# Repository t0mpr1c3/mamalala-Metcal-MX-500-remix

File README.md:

# Sources

This is the work of Christian Klippel (mamalala on EEVblog) in 2012-2013, with input from other users on the forum. This repository is an attempt to collate information punlished in the main project thread, https://www.eevblog.com/forum/projects/diy-metcal-13-56-mhz-rf-supply/

I haven't attempted to build the project myself and have no specialist knowledge to bring to bear.

## richard.cs build

http://randomfunprojects.co.uk/metcal.html

### Comment in post #374

"Whilst you could use the original gerbers I would suggest a few changes:
1) Add in pads for the extra 56 pF capacitor.
2) Put some thermal relief in. I've found a lot of areas where something that carries no real current (DC or RF) like a logic pulldown is unsolderable with a small iron because one end is hard-down onto a large area of ground plane.
3) Consider swapping the LCD pinout to the standard one.
4) A little bit of BOM rationalisation would be nice. For example the Aux supply capacitor for the switcher (can't remember the number now) is currently the only 1206 10nF in the design and could have been the same as the 10nF 0805's scattered everywhere.
5) Depending on your skill with surface mount soldering the pads might benefit from tweaking slightly - they're perfect for reflow but a little tight for hand work."

### Comment in post #375

"The mounting holes on the board are 3.2 mm, this is a perfectly normal size for clearance M3 but I suspect that for many people with an electronics-only background getting four tapped holes in position to within perhaps 0.2 mm will be difficult, and being tapped the heatsink holes can't simply be opened out a little bigger. Might I suggest that loose-fitting 3.5 mm or even 4 mm holes might be preferable on a future board revision."

### Comment in post #512

"I built [my toroids] as per the schematic and notes, with 1uH, 1uH, 400n, 11 turns on a T80, 14 turns on a T50 and then 10 on the next T50. It works well and I've made no attempt to optimise it further."

## See also

- https://hackaday.com/2019/06/16/homemade-magic-makes-the-metcal-go/
- https://habr.com/en/post/451246/
- https://github.com/SergeyMax/SolderingStation
- https://www.eevblog.com/forum/reviews/metcal-mx-5200-and-mx-5000-firmware-and-data-eeprom-information/

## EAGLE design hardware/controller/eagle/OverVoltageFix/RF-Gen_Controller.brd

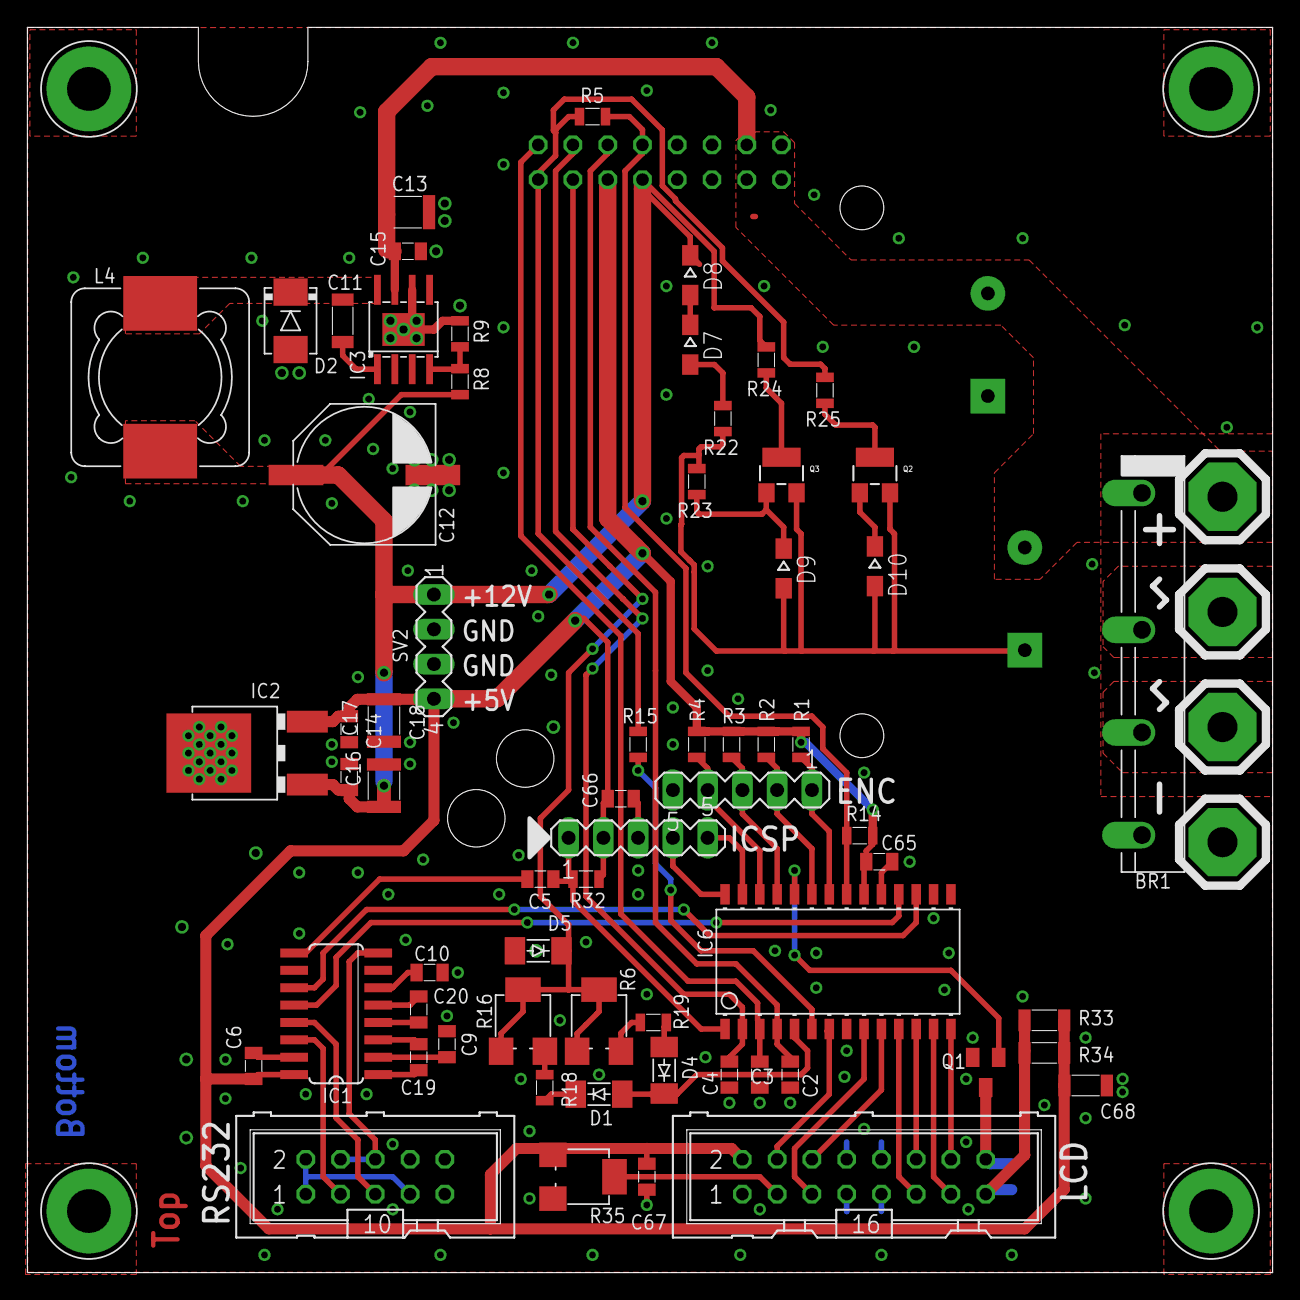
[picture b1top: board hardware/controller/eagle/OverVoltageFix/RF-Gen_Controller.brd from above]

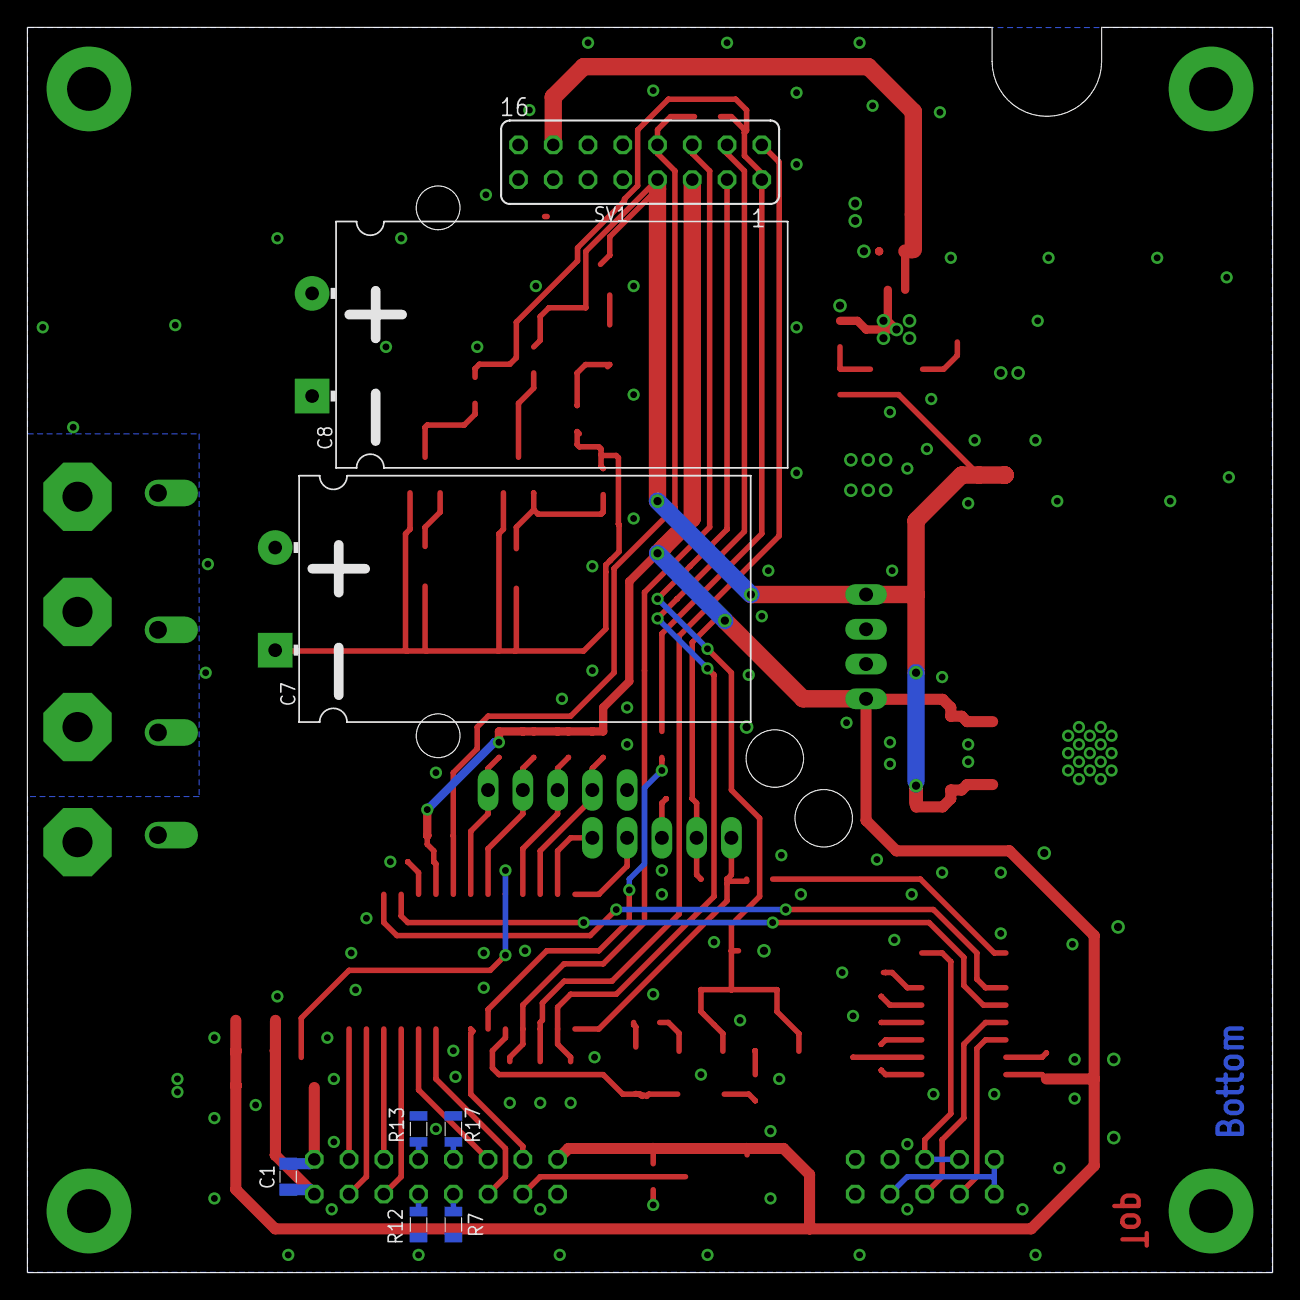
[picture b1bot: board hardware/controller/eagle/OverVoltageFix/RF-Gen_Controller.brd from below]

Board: 2 copper layers, 91.0 x 91.0 mm, 80 parts (8 on the bottom side), 60 nets.

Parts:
BR1: RECTIFIERGBJ_THT; GBJ_THT
C1, C2, C3, C4, C5, C6, C9, C10, C14, C15, C17, C19, C20, C65, C66, C67: 100n; C_0805_REFLOW
C7, C8: 2200µ/50V; CAP_EEUHD1H_VERT2
C11: 10n; C_1206_REFLOW
C12: 150µ/16V; CAP_AL_100_108
C13: 2µ2/50V; C_1210_REFLOW
C16: 4µ7/16V; C_1210_REFLOW
C18: 2µ2/16V; C_1210_REFLOW
C68: 22µ; C_1206_REFLOW
D1, D4: 1N4148; LL-34
D2: SMB
D5: Z5.6; LL-34
D7: 10V; SOD323-W
D8: 12V; SOD323-W
D9, D10: 5V6; SOD323-W
ENC: MA05-1
IC1: SN65C3232SO16; SO16
IC2: DPAK-3
IC3: TPS5430SO-8-PP; SO-8-PP
IC6: PIC18F2620SOIC-28; SOIC-28
ICSP: MA05-1
L4: 47µ; SSR1260
LCD: ML16
PAD1, PAD2, PAD7, PAD8: SOLPAD_5
Q1: 2N7002; SOT23
Q2, Q3: 2N7000; SOT23-W
R1, R2, R3, R4, R7, R12, R13, R17, R24: 22k; R_0805_REFLOW
R5: 0; R_0805_REFLOW
R6, R16, R35: 10k; 3364W
R8: 10k; R_0805_REFLOW
R9: 1k13; R_0805_REFLOW
R14, R32: 47k; R_0805_REFLOW
R15, R23, R25: 1k; R_0805_REFLOW
R18, R19: ***; R_0805_REFLOW
R22: 2k2; R_0805_REFLOW
R33, R34: 10; R_1206_REFLOW
RS232: ML10
SV1: FE08-2
SV2: MA04-1
U$6, U$7, U$8, U$9: MOUNTPADM3_WASHER; PAD_M3_WASHER

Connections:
232_RX: IC1.12, IC6.18
232_TX: IC1.11, IC6.17
+12V: C12.+, C16.P$1, C17.P$1, D8.C, IC2.1, L4.1, R8.P$2, R24.P$2, SV1.7, SV2.1
/MCLR: C5.P$1, IC6.1, ICSP.1, R32.P$1
AC1: BR1.AC1, PAD7.P$1
AC2: BR1.AC2, PAD8.P$1
BL_A: C1.P$2, LCD.15, R33.P$2, R34.P$2
BL_PWM: IC6.24, Q1.1
DB4: IC6.11, LCD.11
DB5: IC6.12, LCD.12
DB6: IC6.13, LCD.13
DB7: IC6.14, LCD.14
DETECT: RS232.1, RS232.2, RS232.7
E: IC6.10, LCD.6
GND: BR1.-, C2.P$2, C3.P$2, C4.P$2, C6.P$2, C7.-, C8.-, C9.P$1, C10.P$1, C12.-, C13.P$2, C14.P$2, C15.P$2, C16.P$2, C17.P$2, C18.P$2, C65.P$2, C66.P$2, C67.P$2, C68.P$2, D2.A, D5.A, D9.A, D9.C, D10.A, ENC.5, IC1.15, IC2.4, IC3.6, IC3.EP, IC6.8, IC6.19, ICSP.3, LCD.1, PAD2.P$1, Q1.2, Q2.2, Q3.1, Q3.2, R7.P$2, R9.P$1, R12.P$2, R13.P$2, R17.P$2, R22.P$1, R23.P$1, R23.P$2, R35.E, RS232.9, SV1.9, SV1.10, SV1.11, SV1.12, SV2.2, SV2.3, U$6.P$1, U$7.P$1, U$8.P$1, U$9.P$1
LED_K: C1.P$1, LCD.16, Q1.3
unnamed: R6.E, R19.P$1
unnamed: R16.E, R18.P$1
unnamed: LCD.9, R12.P$1
unnamed: LCD.7, R7.P$1
unnamed: LCD.10, R13.P$1
unnamed: C9.P$2, IC1.2
unnamed: C5.P$2, IC1.9
unnamed: C10.P$2, IC1.6
unnamed: C11.P$1, IC3.1
unnamed: IC3.4, R8.P$1, R9.P$2
unnamed: C19.P$1, IC1.3
unnamed: C20.P$1, IC1.5
unnamed: LCD.8, R17.P$1
unnamed: D1.C, R18.P$2
unnamed: D4.A, R19.P$2
unnamed: C20.P$2, IC1.4
unnamed: C19.P$2, IC1.1
PGC: IC6.27, ICSP.5
PGD: IC6.28, ICSP.4
REG: C2.P$1, IC6.4, SV1.6
RF_EN: IC6.6, R15.P$2
RF_EN_OUT: C6.P$1, C14.P$1, C18.P$1, C65.P$1, C66.P$1, C67.P$1, C68.P$1, IC1.16, IC2.3, IC6.20, ICSP.2, LCD.2, R1.P$2, R2.P$2, R3.P$2, R4.P$2, R5.P$2, R14.P$2, R15.P$1, R25.P$2, R32.P$2, R33.P$1, R34.P$1, R35.A, SV1.1, SV1.5, SV2.4
RS: IC6.7, LCD.4
RW: IC6.9, LCD.5
RX: IC1.13, RS232.5
S$2: D7.A, R22.P$2
S$3: D7.C, D8.A
S$7: D10.C, Q2.1
S$8: Q3.3, R24.P$1
S$9: Q2.3, R25.P$1
SRESET: IC1.8, RS232.4, RS232.6
SW12: C11.P$2, D2.C, IC3.8, L4.2
TA: ENC.1, IC6.22, R1.P$1
TB: ENC.2, IC6.23, R2.P$1
TC: ENC.3, IC6.25, R3.P$1
TD: ENC.4, IC6.26, R4.P$1
TIP_DET: IC6.21, R5.P$1, R14.P$1, SV1.8
TX: IC1.14, RS232.3
VF: C4.P$1, IC6.2, SV1.4
VIN: BR1.+, C7.+, C8.+, C13.P$1, C15.P$1, IC3.7, PAD1.P$1, SV1.13, SV1.14, SV1.15, SV1.16
VLIM: D5.C, R6.A, R6.S, R16.A, R16.S, SV1.3
VLIM_OUT: D1.A, D4.C, IC6.5
VO: LCD.3, R35.S
VR: C3.P$1, IC6.3, SV1.2

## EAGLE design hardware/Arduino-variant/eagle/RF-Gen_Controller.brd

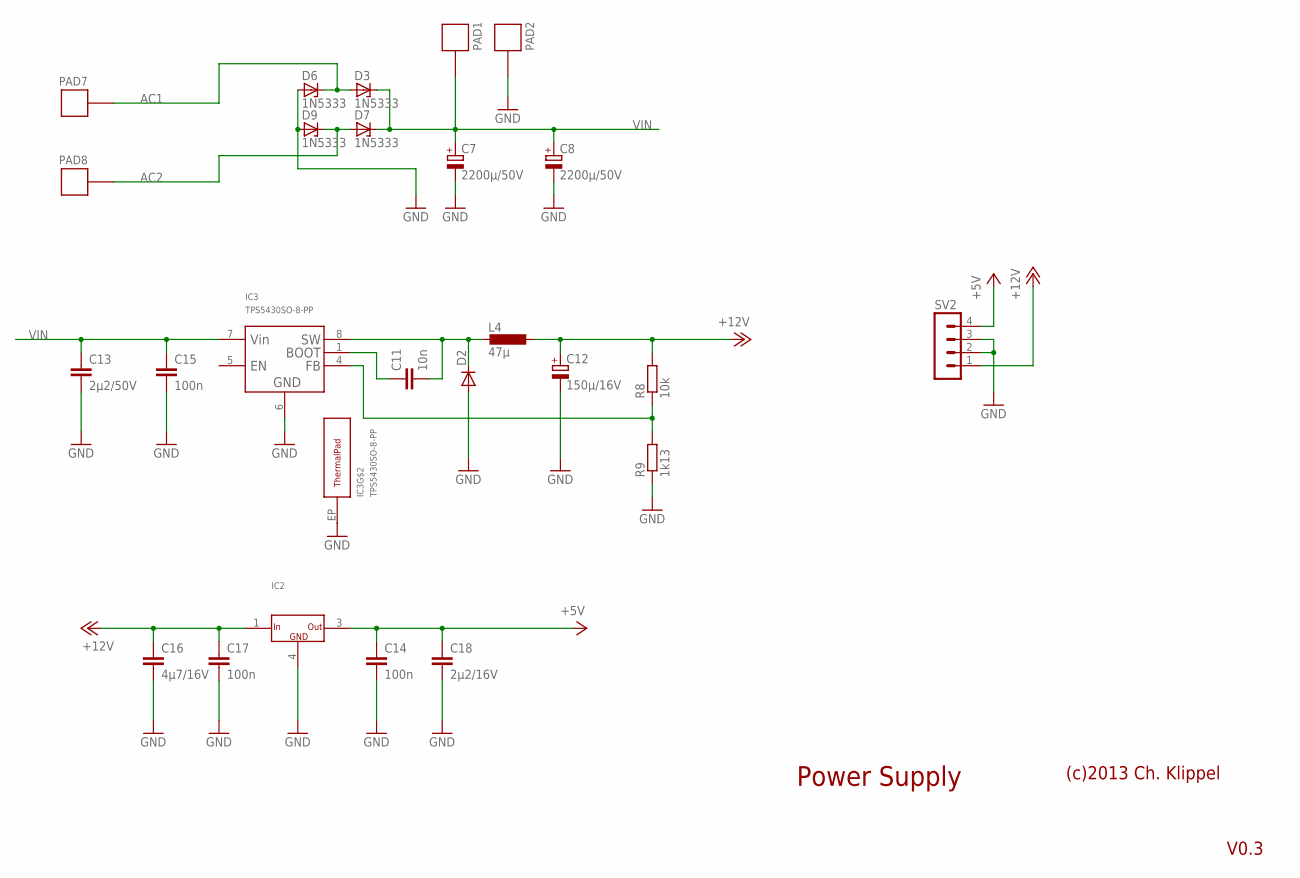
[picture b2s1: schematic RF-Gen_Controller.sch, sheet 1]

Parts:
C7, C8: 2200µ/50V; CAP_EEUHD1H_VERT2
C11: 10n; C_1206_REFLOW
C12: 150µ/16V; CAP_AL_100_108
C13: 2µ2/50V; C_1210_REFLOW
C14, C15, C17: 100n; C_0805_REFLOW
C16: 4µ7/16V; C_1210_REFLOW
C18: 2µ2/16V; C_1210_REFLOW
D2: DIODE-SMB; SMB
D3, D6, D7, D9: 1N5333; C1702-15
IC2: VREG_3DPAK-3; DPAK-3
IC3: TPS5430SO-8-PP; SO-8-PP
L4: 47µ; SSR1260
PAD1, PAD2, PAD7, PAD8: SOLPAD5MM; SOLPAD_5
R8: 10k; R_0805_REFLOW
R9: 1k13; R_0805_REFLOW
SV2: MA04-1

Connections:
+5V: C14.P$1 (1), C18.P$1 (1), IC2.3 (OUT), SV2.4; also elsewhere on the board
+12V: C12.+, C16.P$1 (1), C17.P$1 (1), IC2.1 (IN), L4.1, R8.P$2 (2), SV2.1; also elsewhere on the board
AC1: D3.A, D6.C, PAD7.P$1
AC2: D7.A, D9.C, PAD8.P$1
GND: C7.-, C8.-, C12.-, C13.P$2 (2), C14.P$2 (2), C15.P$2 (2), C16.P$2 (2), C17.P$2 (2), C18.P$2 (2), D2.A, D6.A, D9.A, IC2.4 (GND), IC3.6 (GND), IC3.EP (THERMALPAD), PAD2.P$1, R9.P$1 (1), SV2.2, SV2.3; also elsewhere on the board
unnamed: C11.P$1 (1), IC3.1 (BOOT)
unnamed: IC3.4 (FB), R8.P$1 (1), R9.P$2 (2)
SW12: C11.P$2 (2), D2.C, IC3.8 (SW), L4.2
VIN: C7.+, C8.+, C13.P$1 (1), C15.P$1 (1), D3.C, D7.C, IC3.7 (VIN), PAD1.P$1; also elsewhere on the board

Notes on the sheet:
Power Supply
(c)2013 Ch. Klippel
V0.3

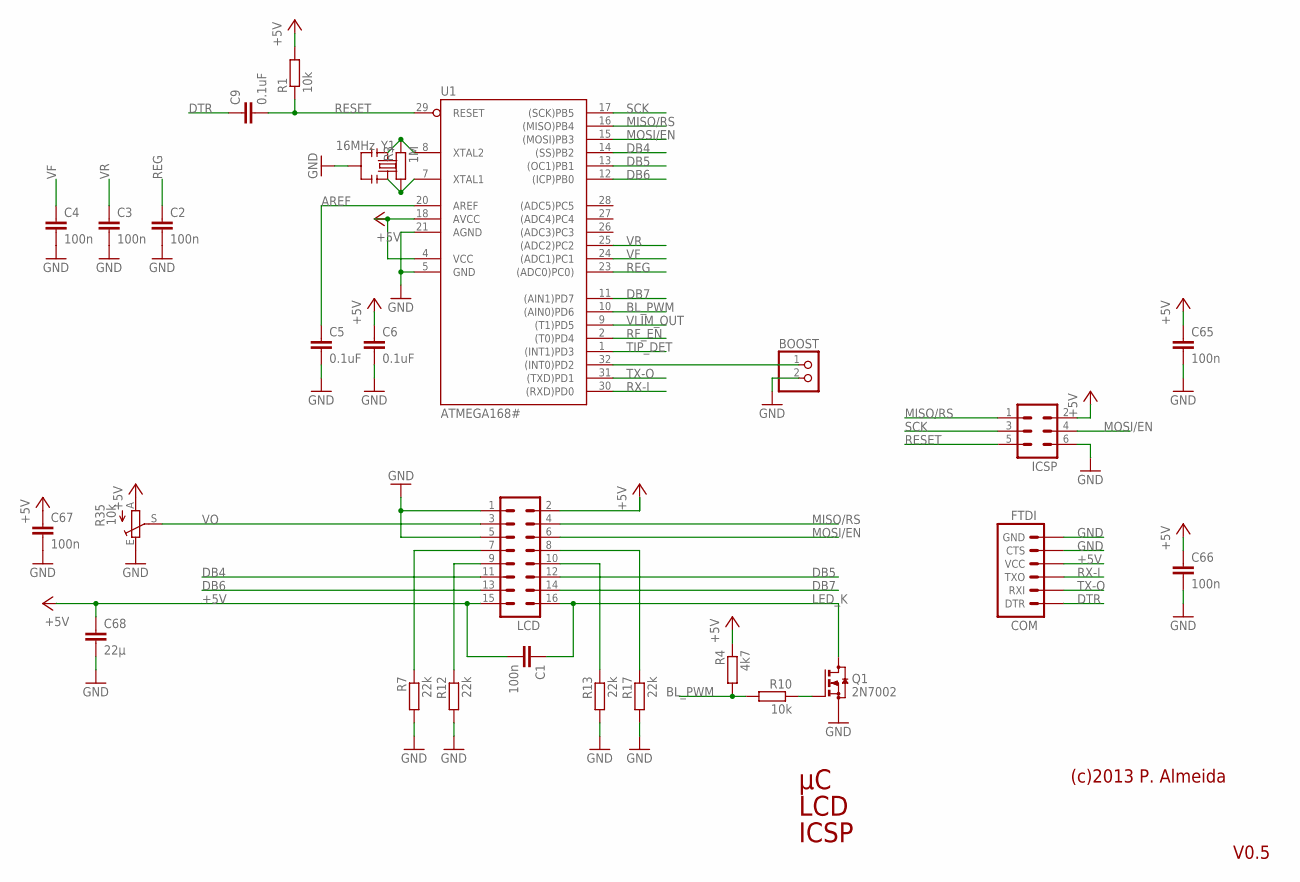
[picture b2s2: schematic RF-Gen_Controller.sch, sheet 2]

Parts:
BOOST: PINHD-1X2/90; 1X02/90
C1, C2, C3, C4, C65, C66, C67: 100n; C_0805_REFLOW
C5, C6, C9: 0.1uF; C_0805_REFLOW
C68: 22µ; C_1206_REFLOW
FTDI: COM; 1X06
ICSP: ML6
LCD: ML16
Q1: 2N7002; SOT23
R1, R10: 10k; R_0805_REFLOW
R3: 1M; R_0805_REFLOW
R4: 4k7; R_0805_REFLOW
R7, R12, R13, R17: 22k; R_0805_REFLOW
R35: 10k; 3364W
U1: ATMEGA168#; TQFP32-08
Y1: 16MHz; RESONATOR-SMD

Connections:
+5V: C1.P$2 (2), C6.P$1 (1), C65.P$1 (1), C66.P$1 (1), C67.P$1 (1), C68.P$1 (1), FTDI.4 (VCC), ICSP.2, LCD.2, LCD.15, R1.P$2 (2), R4.P$1 (1), R35.A, U1.4 (VCC), U1.18 (AVCC); also elsewhere on the board
AREF: C5.P$1 (1), U1.20 (AREF)
BL_PWM: R4.P$2 (2), R10.P$2 (2), U1.10 ((AIN0)PD6)
DB4: LCD.11, U1.14 ((SS)PB2)
DB5: LCD.12, U1.13 ((OC1)PB1)
DB6: LCD.13, U1.12 ((ICP)PB0)
DB7: LCD.14, U1.11 ((AIN1)PD7)
DTR: C9.P$1 (1), FTDI.1 (DTR)
GND: BOOST.2, C2.P$2 (2), C3.P$2 (2), C4.P$2 (2), C5.P$2 (2), C6.P$2 (2), C65.P$2 (2), C66.P$2 (2), C67.P$2 (2), C68.P$2 (2), FTDI.5 (CTS), FTDI.6 (GND), ICSP.6, LCD.1, LCD.5, Q1.2 (S), R7.P$2 (2), R12.P$2 (2), R13.P$2 (2), R17.P$2 (2), R35.E, U1.5 (GND), U1.21 (AGND), Y1.2; also elsewhere on the board
LED_K: C1.P$1 (1), LCD.16, Q1.3 (D)
MISO/RS: ICSP.1, LCD.4, U1.16 ((MISO)PB4)
MOSI/EN: ICSP.4, LCD.6, U1.15 ((MOSI)PB3)
unnamed: LCD.9, R12.P$1 (1)
unnamed: LCD.7, R7.P$1 (1)
unnamed: LCD.10, R13.P$1 (1)
unnamed: Q1.1 (G), R10.P$1 (1)
unnamed: BOOST.1, U1.32 ((INT0)PD2)
unnamed: R3.P$1 (1), U1.8 (XTAL2), Y1.1
unnamed: R3.P$2 (2), U1.7 (XTAL1), Y1.3
unnamed: LCD.8, R17.P$1 (1)
REG: C2.P$1 (1), U1.23 ((ADC0)PC0)); also elsewhere on the board
RESET: C9.P$2 (2), ICSP.5, R1.P$1 (1), U1.29 (RESET)
RF_EN: U1.2 ((T0)PD4); also elsewhere on the board
RX-I: FTDI.3 (TXO), U1.30 ((RXD)PD0)
SCK: ICSP.3, U1.17 ((SCK)PB5)
TIP_DET: U1.1 ((INT1)PD3); also elsewhere on the board
TX-O: FTDI.2 (RXI), U1.31 ((TXD)PD1)
VF: C4.P$1 (1), U1.24 ((ADC1)PC1); also elsewhere on the board
VLIM_OUT: U1.9 ((T1)PD5); also elsewhere on the board
VO: LCD.3, R35.S
VR: C3.P$1 (1), U1.25 ((ADC2)PC2); also elsewhere on the board

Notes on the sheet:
LCD
ICSP
(c)2013 P. Almeida
V0.5

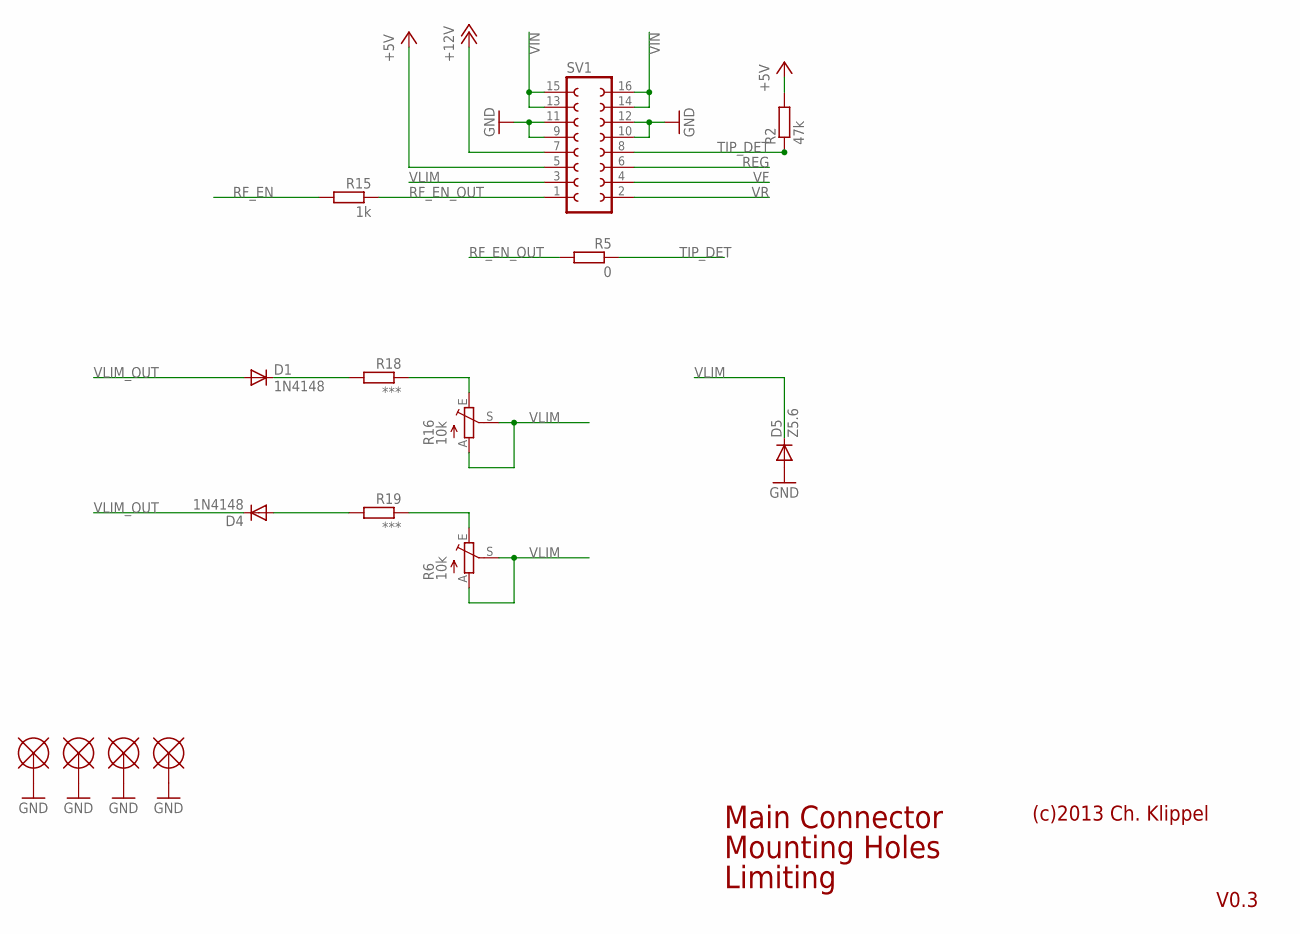
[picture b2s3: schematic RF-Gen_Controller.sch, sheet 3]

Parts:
D1, D4: 1N4148; LL-34
D5: Z5.6; LL-34
R2: 47k; R_0805_REFLOW
R5: 0; R_0805_REFLOW
R6, R16: 10k; 3364W
R15: 1k; R_0805_REFLOW
R18, R19: ***; R_0805_REFLOW
SV1: FE08-2
U$6, U$7, U$8, U$9: MOUNTPADM3_WASHER; PAD_M3_WASHER

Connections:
+5V: R2.P$2 (2), SV1.5; also elsewhere on the board
+12V: SV1.7; also elsewhere on the board
GND: D5.A, SV1.9, SV1.10, SV1.11, SV1.12, U$6.P$1, U$7.P$1, U$8.P$1, U$9.P$1; also elsewhere on the board
unnamed: R6.E, R19.P$1 (1)
unnamed: R16.E, R18.P$1 (1)
unnamed: D1.C, R18.P$2 (2)
unnamed: D4.A, R19.P$2 (2)
REG: SV1.6; also elsewhere on the board
RF_EN: R15.P$2 (2); also elsewhere on the board
RF_EN_OUT: R5.P$2 (2), R15.P$1 (1), SV1.1
TIP_DET: R2.P$1 (1), R5.P$1 (1), SV1.8; also elsewhere on the board
VF: SV1.4; also elsewhere on the board
VIN: SV1.13, SV1.14, SV1.15, SV1.16; also elsewhere on the board
VLIM: D5.C, R6.A, R6.S, R16.A, R16.S, SV1.3
VLIM_OUT: D1.A, D4.C; also elsewhere on the board
VR: SV1.2; also elsewhere on the board

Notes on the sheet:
Main Connector
Mounting Holes
Limiting
(c)2013 Ch. Klippel
V0.3

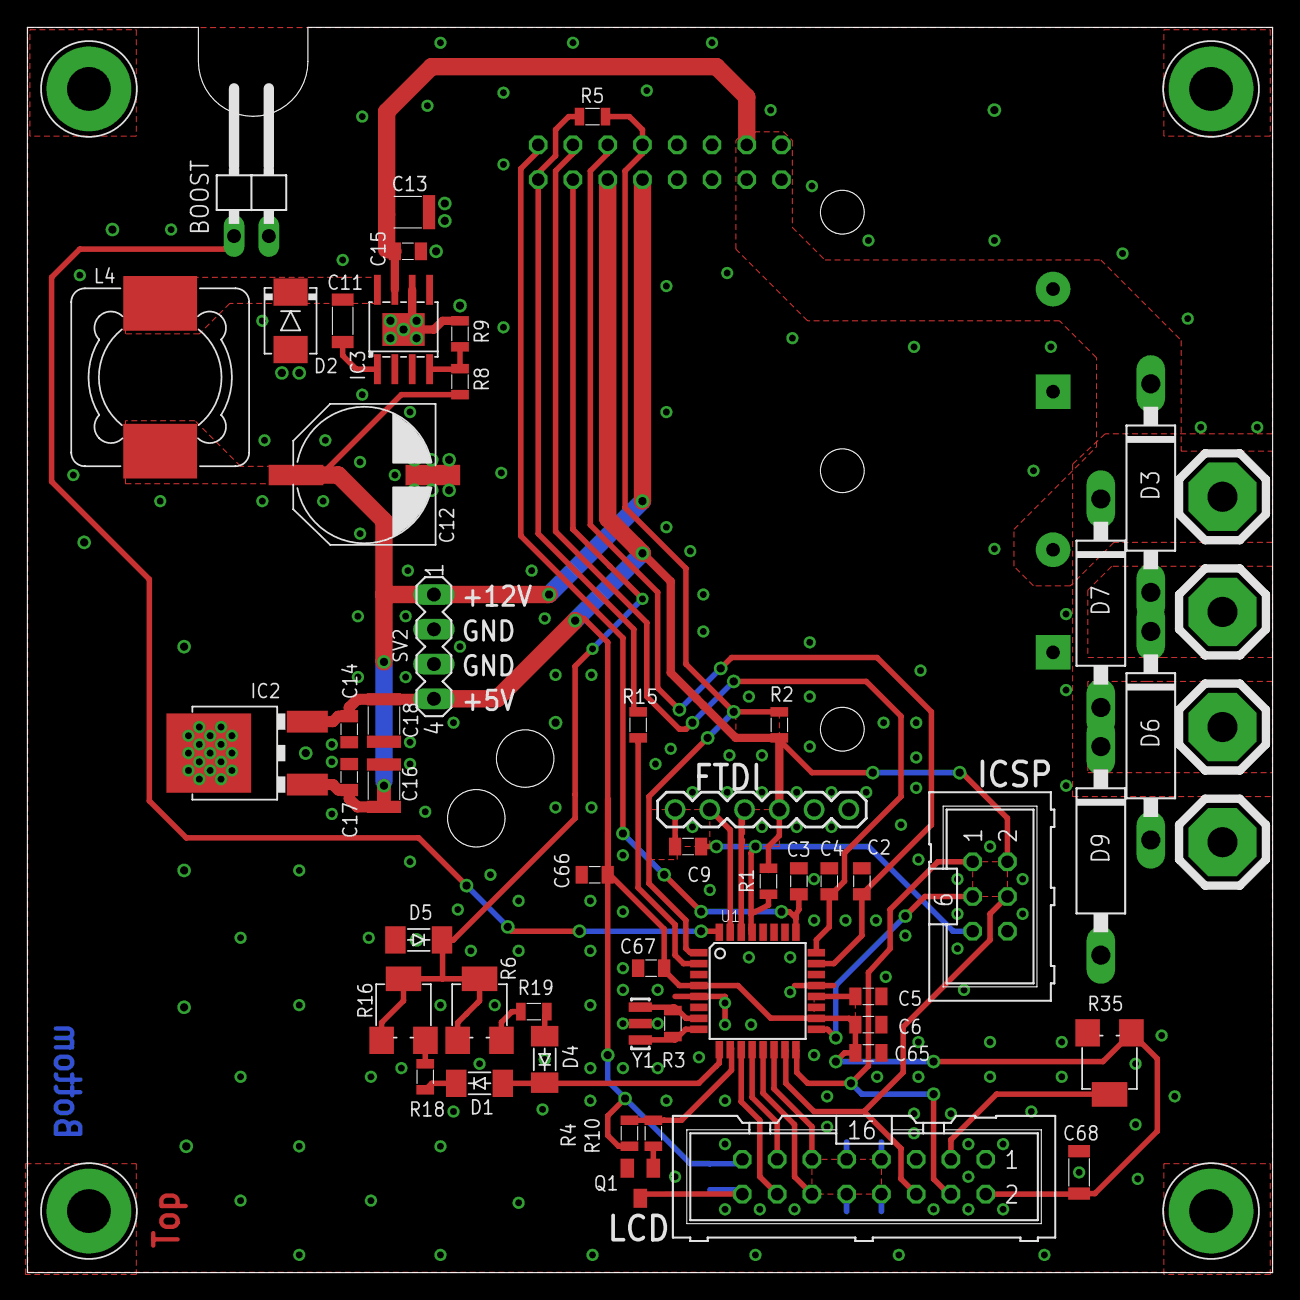
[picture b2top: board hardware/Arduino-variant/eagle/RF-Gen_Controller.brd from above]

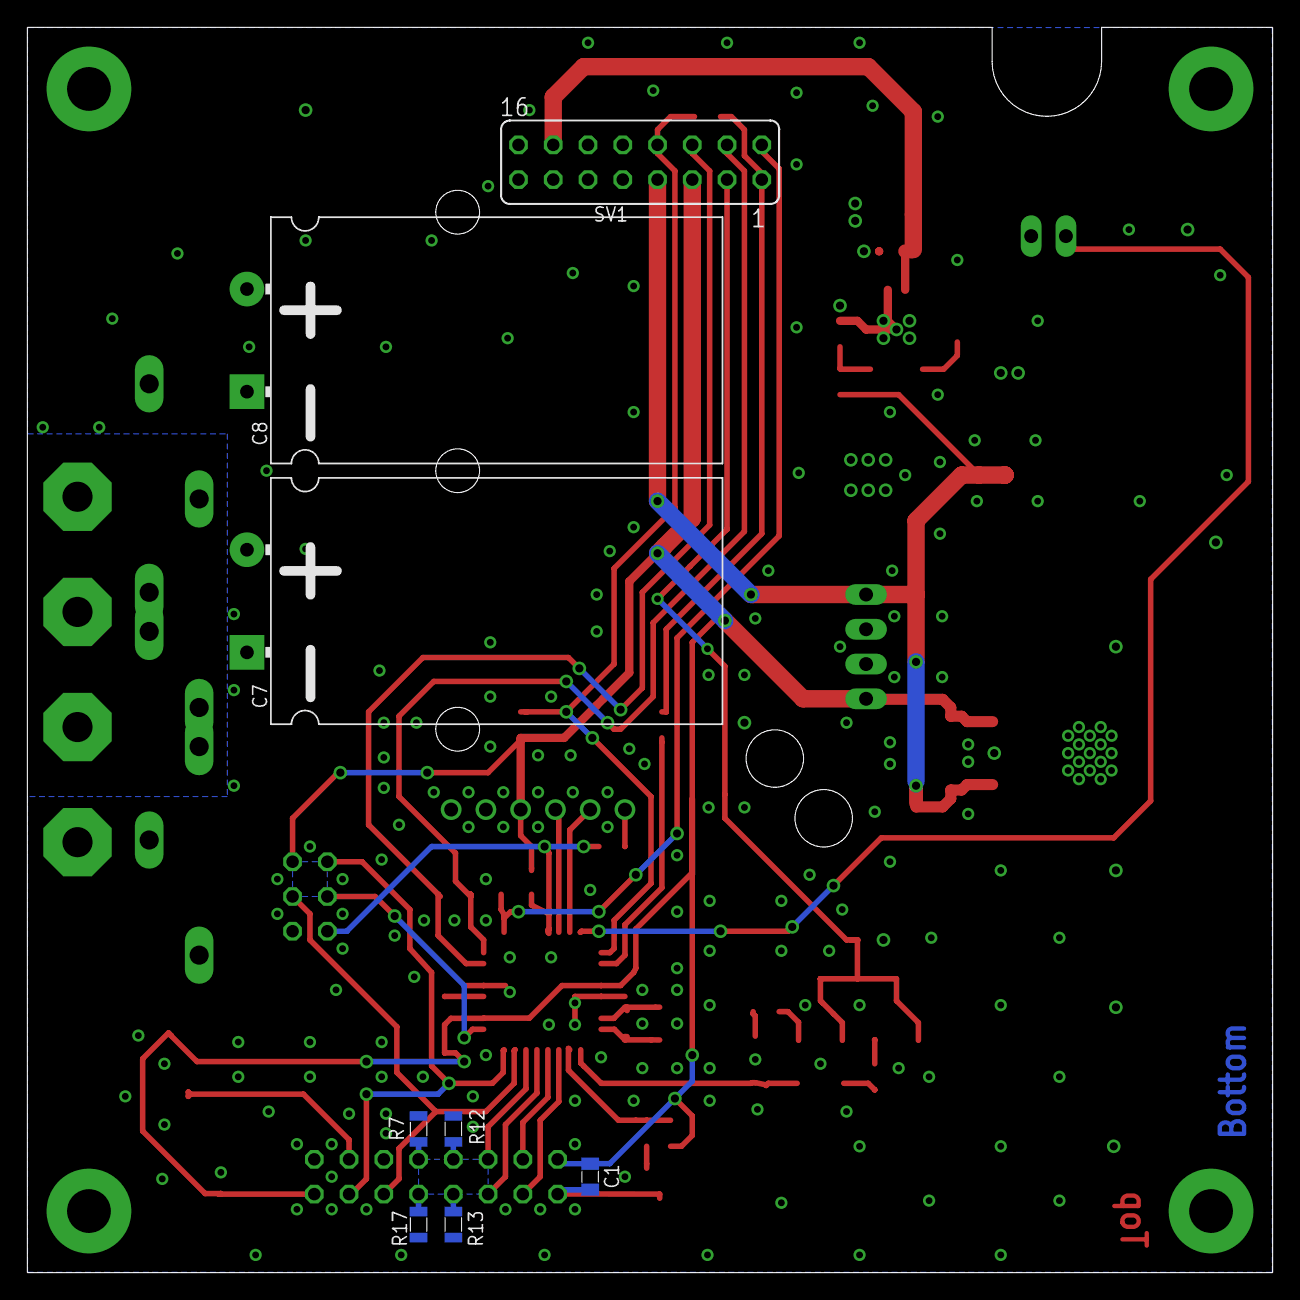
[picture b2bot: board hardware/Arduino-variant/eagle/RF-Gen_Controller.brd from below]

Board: 2 copper layers, 91.0 x 91.0 mm, 67 parts (8 on the bottom side), 44 nets.

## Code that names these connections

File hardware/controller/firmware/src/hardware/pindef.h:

/*
 * (c) 2013 Ch. klippel  -  ck@atelier-klippel.de / c.klippel@gmx.de
 *
 * This code is released under the terms of the GPL, version 2 or newer.
 * See the file COPYING for more information about the license.
 *
 * Changelog:
 *
 * v00.01: - Initial version
 *
 */

#ifndef PINDEF_H
#define PINDEF_H

#define PIN_IN		1
#define PIN_OUT		0

// 1 = in, 0 = out

#define CFG_TRISA	0b00001111;
#define CFG_LATA	0b00000000;

#define CFG_TRISB	0b00110111;
#define CFG_LATB	0b00000000;

#define CFG_TRISC	0b10000000;
#define CFG_LATC	0b00000000;

#define V_FORWARD_IN            PORTAbits.RA0
#define V_REFLECTED_IN          PORTAbits.RA1
#define V_REG_IN		PORTAbits.RA2

#define VLIM_OUT		LATAbits.LATA3
#define VLIM_DIR		TRISAbits.TRISA3

#define RFG_EN			LATAbits.LATA4

#define TIP_DET 		PORTBbits.RB0

#define ENC1_A			PORTBbits.RB1
#define ENC1_B			PORTBbits.RB2
#define ENC1_K			PORTBbits.RB4
#define ENC1_S			PORTBbits.RB5


#define BL			LATBbits.LATB3
#define BL_ON			1
#define BL_OFF			0

#define PGD				PORTBbits.RB7
#define PGC				PORTBbits.RB6

#define MCLR			PORTEbits.RE3

#endif

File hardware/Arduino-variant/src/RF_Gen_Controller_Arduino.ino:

#include <LiquidCrystal.h>

LiquidCrystal lcd(12, 11, 10, 9, 8, 7); // LiquidCrystal(rs, enable, d4, d5, d6, d7)

int TIP_DET_PIN           = 3;          // Digital PIN 0-13
int RF_EN_PIN             = 4;          // Digital PIN 0-13
int VLIM_PIN              = 5;          // Digital PIN 0-13
int BOOST_PIN             = 2;          // Digital PIN 0-13
int REG_PIN               = A0;         // Analog PIN A0-A5
int VF_PIN                = A1;         // Analog PIN A0-A5
int VR_PIN                = A2;         // Analog PIN A0-A5
int BACKLIGHT_PIN         = 6;          // PWM PIN 3, 5, 6, 9, 10, or 11

float VF, VR, REG, VSWR;

int SAMPLES               = 16;
int NO_TIP_BACKLIGHT_VAL  = 50;         // 0-255
int POWER_BACKLIGHT_VAL   = 255;        // 0-255
int BOOST_BACKLIGHT_VAL   = 255;        // 0-255
int READY_BACKLIGHT_VAL   = 255;        // 0-255
int ECO_BACKLIGHT_VAL     = 50;         // 0-255
int STANDBY_BACKLIGHT_VAL = 0;          // 0-255

int VSWR_MAX              = 1000;
int READY_VAL             = 10;         // 0-99
    
long ECO_TIME             = 5000;       // ms
long STANDBY_TIME         = 10000;      // ms
  
unsigned long LASTMILLIS;
int PERCENT, LASTPERCENT, STATE, LASTSTATE;

byte r0[8] = {
  B00000, 
  B00000,
  B00000,
  B00000,
  B00000,
  B00000,
  B00000,
  B00000
}; // 0 / 5
byte r1[8] = {
  B10000, 
  B10000,
  B10000,
  B10000,
  B10000,
  B10000,
  B10000,
  B10000
}; // 1 / 5
byte r2[8] = {
  B11000, 
  B11000,
  B11000,
  B11000,
  B11000,
  B11000,
  B11000,
  B11000
}; // 2 / 5 
byte r3[8] = {
  B11100, 
  B11100,
  B11100,
  B11100,
  B11100,
  B11100,
  B11100,
  B11100
}; // 3 / 5
byte r4[8] = {
  B11110, 
  B11110,
  B11110,
  B11110,
  B11110,
  B11110,
  B11110,
  B11110
}; // 4 / 5
byte r5[8] = {
  B11111, 
  B11111,
  B11111,
  B11111,
  B11111,
  B11111,
  B11111,
  B11111
}; // 5 / 5

void draw_state(int State) {
  
  if (State == 0){
      lcd.setCursor(4, 0);
      lcd.print("STANDBY");
      digitalWrite(RF_EN_PIN, LOW);
      analogWrite(BACKLIGHT_PIN, STANDBY_BACKLIGHT_VAL);}
      
  if (State == 1){
      lcd.setCursor(4, 0);
      lcd.print("  ECO  ");
      pinMode(VLIM_PIN, OUTPUT);
      digitalWrite(VLIM_PIN, HIGH);
      analogWrite(BACKLIGHT_PIN, ECO_BACKLIGHT_VAL);}
      
  if (State == 2){
      lcd.setCursor(4, 0);
      lcd.print(" READY ");
      pinMode(VLIM_PIN, INPUT);
      analogWrite(BACKLIGHT_PIN, READY_BACKLIGHT_VAL);}
      
  if (State == 3){
      lcd.setCursor(4, 0);
      lcd.print(" POWER ");
      pinMode(VLIM_PIN, INPUT);
      analogWrite(BACKLIGHT_PIN, POWER_BACKLIGHT_VAL);}
      
  if (State == 4){
      lcd.setCursor(4, 0);
      lcd.print(" BOOST ");
      digitalWrite(RF_EN_PIN, HIGH);
      pinMode(VLIM_PIN, OUTPUT);
      digitalWrite(VLIM_PIN, LOW);
      analogWrite(BACKLIGHT_PIN, BOOST_BACKLIGHT_VAL);}
      
  if (State == 5){
      lcd.setCursor(4, 0);
      lcd.print("NO  TIP");
      digitalWrite(RF_EN_PIN, LOW);
      analogWrite(BACKLIGHT_PIN, NO_TIP_BACKLIGHT_VAL);}
  
}

void draw_bargraph(int percent) {
  int i, cp, cl;

  if (percent < READY_VAL){
      lcd.setCursor(14, 1);
      lcd.print("0");
      lcd.print(percent);}
  else { 
      lcd.setCursor(14, 1);
      lcd.print(percent);}

  lcd.setCursor(0, 1);
  
  percent = map(percent, 0, 99, 0, 70);
  cp = percent / 5;
  cl = percent % 5;
  
  for(i = 0; i < cp; ++i)
    lcd.write(5);
  if(cl != 0)
    lcd.write(cl);

  for(i = 0; i < 14 - (cp + (cl ? 1 : 0)); ++i)
    lcd.write((uint8_t)0);
}

void setup(){
  
  Serial.begin(9600);
  pinMode(TIP_DET_PIN, INPUT);
  digitalWrite(TIP_DET_PIN, HIGH);
  pinMode(BOOST_PIN, INPUT);
  digitalWrite(BOOST_PIN, HIGH);
  pinMode(RF_EN_PIN, OUTPUT);
  pinMode(BACKLIGHT_PIN, OUTPUT);
  analogWrite(BACKLIGHT_PIN, BOOST_BACKLIGHT_VAL);
   
  lcd.createChar(0, r0);
  lcd.createChar(1, r1);
  lcd.createChar(2, r2);
  lcd.createChar(3, r3);
  lcd.createChar(4, r4);
  lcd.createChar(5, r5);

  lcd.begin(16, 2); 
  lcd.clear();
  lcd.setCursor(0, 0);
  lcd.print(" RF-GEN MX-5000 ");
  lcd.setCursor(0, 1);
  lcd.print("   Ver:  2.01   ");
  delay(3000);
  lcd.clear();
  
  PERCENT = 0;
  STATE = 4;
  draw_state(STATE);
  LASTSTATE = STATE;
  draw_bargraph(PERCENT);
  LASTPERCENT = PERCENT;
}

void loop(){
  
REG = 0;
VF  = 0;
VR  = 0;

for (int i = 0; i < SAMPLES; i++){
     REG = REG + analogRead(REG_PIN);
     VF  = VF + analogRead(VF_PIN);
     VR  = VR + analogRead(VR_PIN);
     delay(1);}
     
REG = REG / SAMPLES;
VF  = VF / SAMPLES;
VR  = VR / SAMPLES;

VSWR = (1 + sqrt(VR / VF)) / (1 - sqrt(VR / VF));
PERCENT = map(constrain(VSWR, 0, VSWR_MAX), 0, VSWR_MAX, 99, 0);

Serial.print("REG = ");
Serial.print(REG);
Serial.print("\tVF = ");
Serial.print(VF);
Serial.print("\tVR = ");
Serial.print(VR);
Serial.print("\tVSWR = ");
Serial.print(VSWR);
Serial.print("\tPERCENT = ");
Serial.println(PERCENT);

if (digitalRead(TIP_DET_PIN) == LOW) STATE = 5;                                                     //NO TIP 

else{  
  
if (digitalRead(BOOST_PIN) == LOW) STATE = 4;
  
else {
  
if (LASTPERCENT > PERCENT && LASTSTATE == 4 || PERCENT > READY_VAL && LASTSTATE != 4)  STATE = 3;   //POWER
if (PERCENT > READY_VAL && LASTSTATE == 1 || LASTSTATE == 5)                           STATE = 4;   //BOOST
if (PERCENT < READY_VAL && LASTSTATE != 1 && LASTSTATE != 4 && LASTSTATE != 5)         STATE = 2;   //READY
if (millis() - LASTMILLIS > ECO_TIME)                                                  STATE = 1;   //ECO
if (millis() - LASTMILLIS > STANDBY_TIME)                                              STATE = 0;   //STANDBY
}
}

if (PERCENT > READY_VAL || STATE == 4 || STATE == 5) LASTMILLIS = millis();

if (STATE != LASTSTATE){
    draw_state(STATE);
    LASTSTATE = STATE;}
  
if (PERCENT != LASTPERCENT){
    draw_bargraph(PERCENT);
    LASTPERCENT = PERCENT;}
  
delay(100);
}

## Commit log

2021-02-20 remove inconsistencies in build notes and BOM

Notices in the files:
hardware/Arduino-variant/eagle/RF-Gen_Controller.brd:
(c) 2013 C. Klippel/P. Almeida
hardware/controller/eagle/OverVoltageFix/RF-Gen_Controller.brd:
(c) 2012 Christian Klippel
parts and their libraries:
SparkFun-PowerSymbols: Licensing: Creative Commons ShareAlike 4.0 International - https://creativecommons.org/licenses/by-sa/4.0
